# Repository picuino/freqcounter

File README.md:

Frequency counter
=================
This is a cheap and simple but powerful frequency counter capable 
of measurements of frequency with 8 digits of resolution every second
(9 digits of resolution in 10 second averages).

This frequency counter is based on a little **PIC 16F18446** a 
16x2 LCD display (optional) and USB-Serial interface with PC.

All the programs and hardware designs are free, open source and
open hardware.

The frequency counter have a Command Line Interface via serial 
communications for manage multiple internal options. 
You can read more in [Command Line Interface help](docs/commands.md)

You can mount the frequency counter over a breadboard with this simple 
[schematic](breadboard/kicad/freqcounter_16F18446.pdf)
with a cost of few dollars.
The LDC display is optional. All the info is sended via serial.

Specifications
--------------
* Input frequency range: 0.01 Hz to 15MHz
* Resolution: 8 digits per second (10ns of resolution) at all frequencies.
* Precision: 0.1PPM with simple crystal and calibration.
* Number of inputs: 2 TTL inputs + 1 Zero Cross Detection input
* Output: Frequency or Period, time and pulses counted.
* Phase delay: between 2 inputs with 10ns of resolution.
* Gate times: 1 second and 0.1 seconds.
* Output: via LCD (optional) and serial UART.
* Autocalibration: with 1PPS signal or with 10MHz signal.
* Reciprocal counting: allow calculate lower frequencies with decimals.
* Continuous timestamp: allow frequency averages without error.
* Frequency autorange from Mega Hertz to milli Hertz.
* Adaptable system frequency without reprogramming (8MHz internal or 5MHz external)
* Command Line Interface: via USB-serial communications for configuring options.
* Input levels: between 0.8v (LOW) and 3.1V (HIGH).
* Power Supply: 5 volts.
* DIY: you can mount it with a breadboard and one crystal oscillator.

Images
------
Example of frequency meter conected to an Arduino.
Arduino gives power and serial communications with PC.

Orange cables are the 2 TTL inputs.

[Full image](images/IMG_20200427_143115.jpg)

Licenses
--------

* Creative Commons Atribution-ShareAlike version 4, for hardware designs,
  texts, photograps, layouts, schematics, and similar.

* GNU General Public License version 3, for microcontroller 
  and computer programs.

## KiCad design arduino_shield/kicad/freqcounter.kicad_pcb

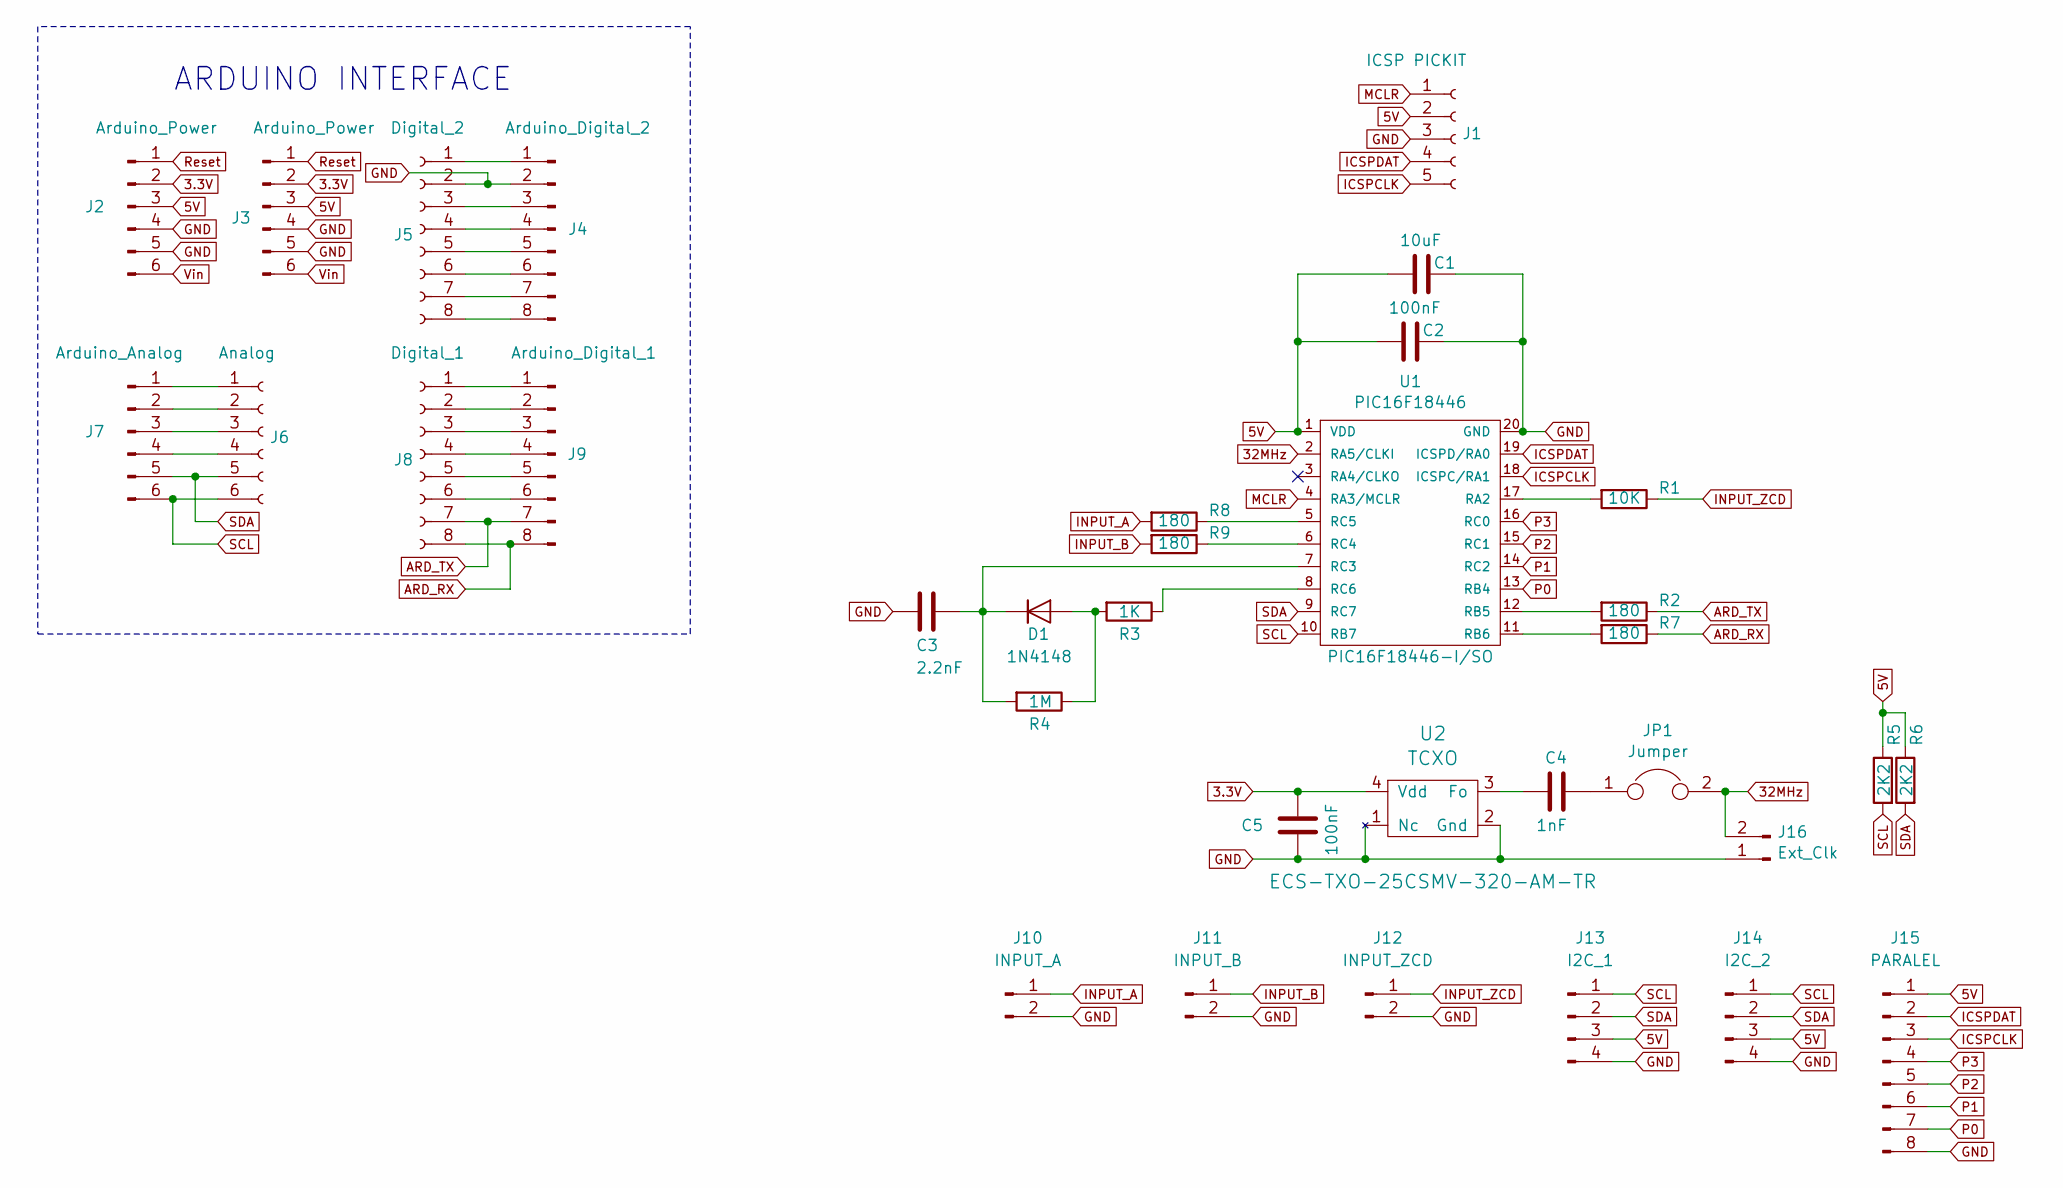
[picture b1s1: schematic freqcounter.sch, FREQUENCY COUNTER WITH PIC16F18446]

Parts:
C1: 10uF; C_0805_2012Metric_Pad1.15x1.40mm_HandSolder
C2, C5: 100nF; C_0805_2012Metric_Pad1.15x1.40mm_HandSolder
C3: 2.2nF; C_0805_2012Metric_Pad1.15x1.40mm_HandSolder
C4: 1nF; C_0805_2012Metric_Pad1.15x1.40mm_HandSolder
D1: 1N4148; SOD-80_HandSolder
J1: ICSP PICKIT; PinHeader_1x05_P2.54mm_Vertical
J2, J3: Arduino_Power; Connector_1x06
J4: Arduino_Digital_2; Connector_1x08
J5: Digital_2; Connector_1x08
J6: Analog; Connector_1x06
J7: Arduino_Analog; Connector_1x06
J8: Digital_1; Connector_1x08
J9: Arduino_Digital_1; Connector_1x08
J10: INPUT_A; PinHeader_1x02_P2.54mm_Vertical
J11: INPUT_B; PinHeader_1x02_P2.54mm_Vertical
J12: INPUT_ZCD; PinHeader_1x02_P2.54mm_Vertical
J13: I2C_1; PinHeader_1x04_P2.54mm_Vertical
J14: I2C_2; PinHeader_1x04_P2.54mm_Vertical
J15: PARALEL; Connector_1x08
J16: Ext_Clk; PinHeader_1x02
JP1: Jumper; PinHeader_1x02
R1: 10K; R_0805_2012Metric_Pad1.15x1.40mm_HandSolder
R2, R7, R8, R9: 180; R_0805_2012Metric_Pad1.15x1.40mm_HandSolder
R3: 1K; R_0805_2012Metric_Pad1.15x1.40mm_HandSolder
R4: 1M; R_0805_2012Metric_Pad1.15x1.40mm_HandSolder
R5, R6: 2K2; R_0805_2012Metric_Pad1.15x1.40mm_HandSolder
U1: PIC16F18446; SOIC-20W_7.5x12.8mm_P1.27mm
U2: TCXO; TCXO-5032

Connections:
3.3V: C5.2, J2.2, J3.2, U2.4 (Vdd)
5V: C1.2, C2.2, J1.2, J2.3, J3.3, J13.3, J14.3, J15.1, R5.1, R6.1, U1.1 (VDD)
32MHz: J16.2, JP1.2, U1.2 (RA5/CLKI)
ARD_RX: J8.8, J9.8, R7.1
ARD_TX: J8.7, J9.7, R2.1
GND: C1.1, C2.1, C3.2, C5.1, J1.3, J2.4, J2.5, J3.4, J3.5, J4.2, J5.2, J10.2, J11.2, J12.2, J13.4, J14.4, J15.8, J16.1, U1.20 (GND), U2.1 (Nc), U2.2 (Gnd)
ICSPCLK: J1.5, J15.3, U1.18 (ICSPC/RA1)
ICSPDAT: J1.4, J15.2, U1.19 (ICSPD/RA0)
INPUT_A: J10.1, R8.2
INPUT_B: J11.1, R9.2
INPUT_ZCD: J12.1, R1.1
MCLR: J1.1, U1.4 (RA3/MCLR)
unnamed: C3.1, D1.1 (K), R4.2, U1.7 (RC3)
unnamed: C4.1, U2.3 (Fo)
unnamed: C4.2, JP1.1
unnamed: D1.2 (A), R3.2, R4.1
unnamed: J4.1, J5.1
unnamed: J4.3, J5.3
unnamed: J4.4, J5.4
unnamed: J4.5, J5.5
unnamed: J4.6, J5.6
unnamed: J4.7, J5.7
unnamed: J4.8, J5.8
unnamed: J6.1, J7.1
unnamed: J6.2, J7.2
unnamed: J6.3, J7.3
unnamed: J6.4, J7.4
unnamed: J8.1, J9.1
unnamed: J8.2, J9.2
unnamed: J8.3, J9.3
unnamed: J8.4, J9.4
unnamed: J8.5, J9.5
unnamed: J8.6, J9.6
unnamed: R1.2, U1.17 (RA2)
unnamed: R2.2, U1.12 (RB5)
unnamed: R3.1, U1.8 (RC6)
unnamed: R7.2, U1.11 (RB6)
unnamed: R8.1, U1.5 (RC5)
unnamed: R9.1, U1.6 (RC4)
P0: J15.7, U1.13 (RB4)
P1: J15.6, U1.14 (RC2)
P2: J15.5, U1.15 (RC1)
P3: J15.4, U1.16 (RC0)
Reset: J2.1, J3.1
SCL: J6.6, J7.6, J13.1, J14.1, R5.2, U1.10 (RB7)
SDA: J6.5, J7.5, J13.2, J14.2, R6.2, U1.9 (RC7)
Vin: J2.6, J3.6

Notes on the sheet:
ARDUINO INTERFACE

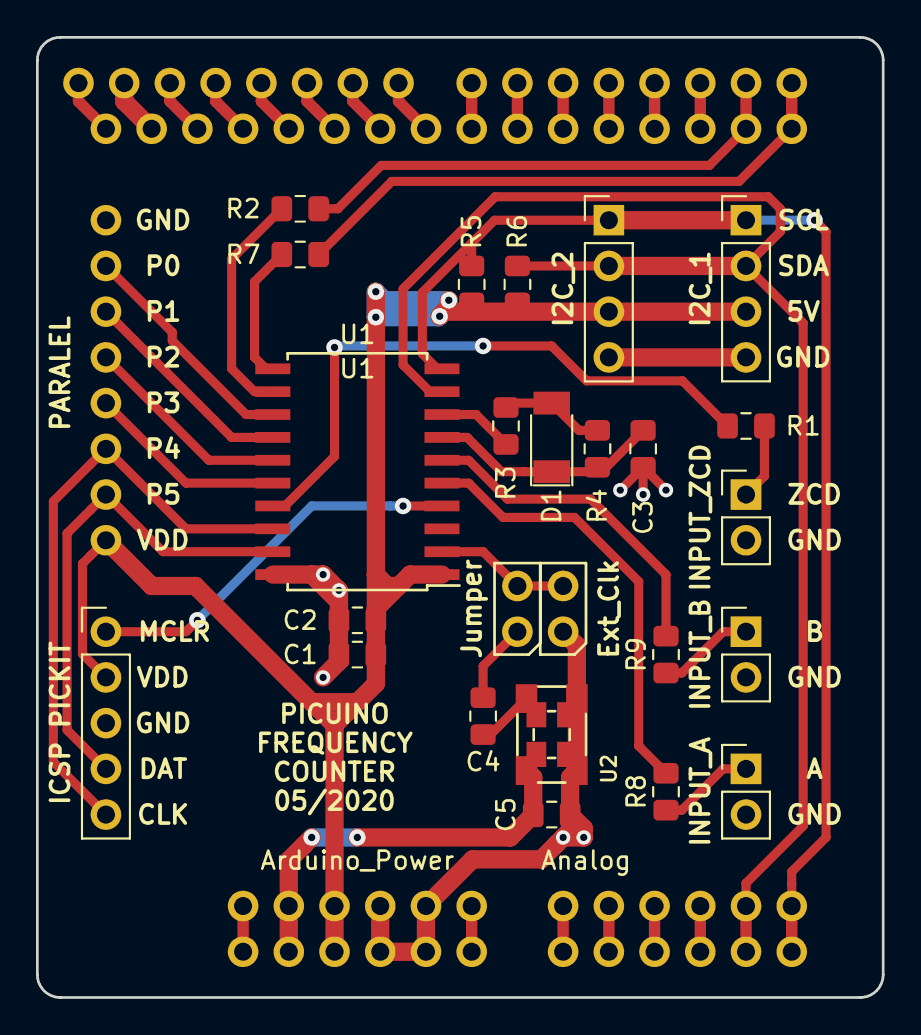
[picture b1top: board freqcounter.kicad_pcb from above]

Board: 2 copper layers, 47.0 x 53.3 mm, 34 parts (0 on the bottom side), 47 nets.

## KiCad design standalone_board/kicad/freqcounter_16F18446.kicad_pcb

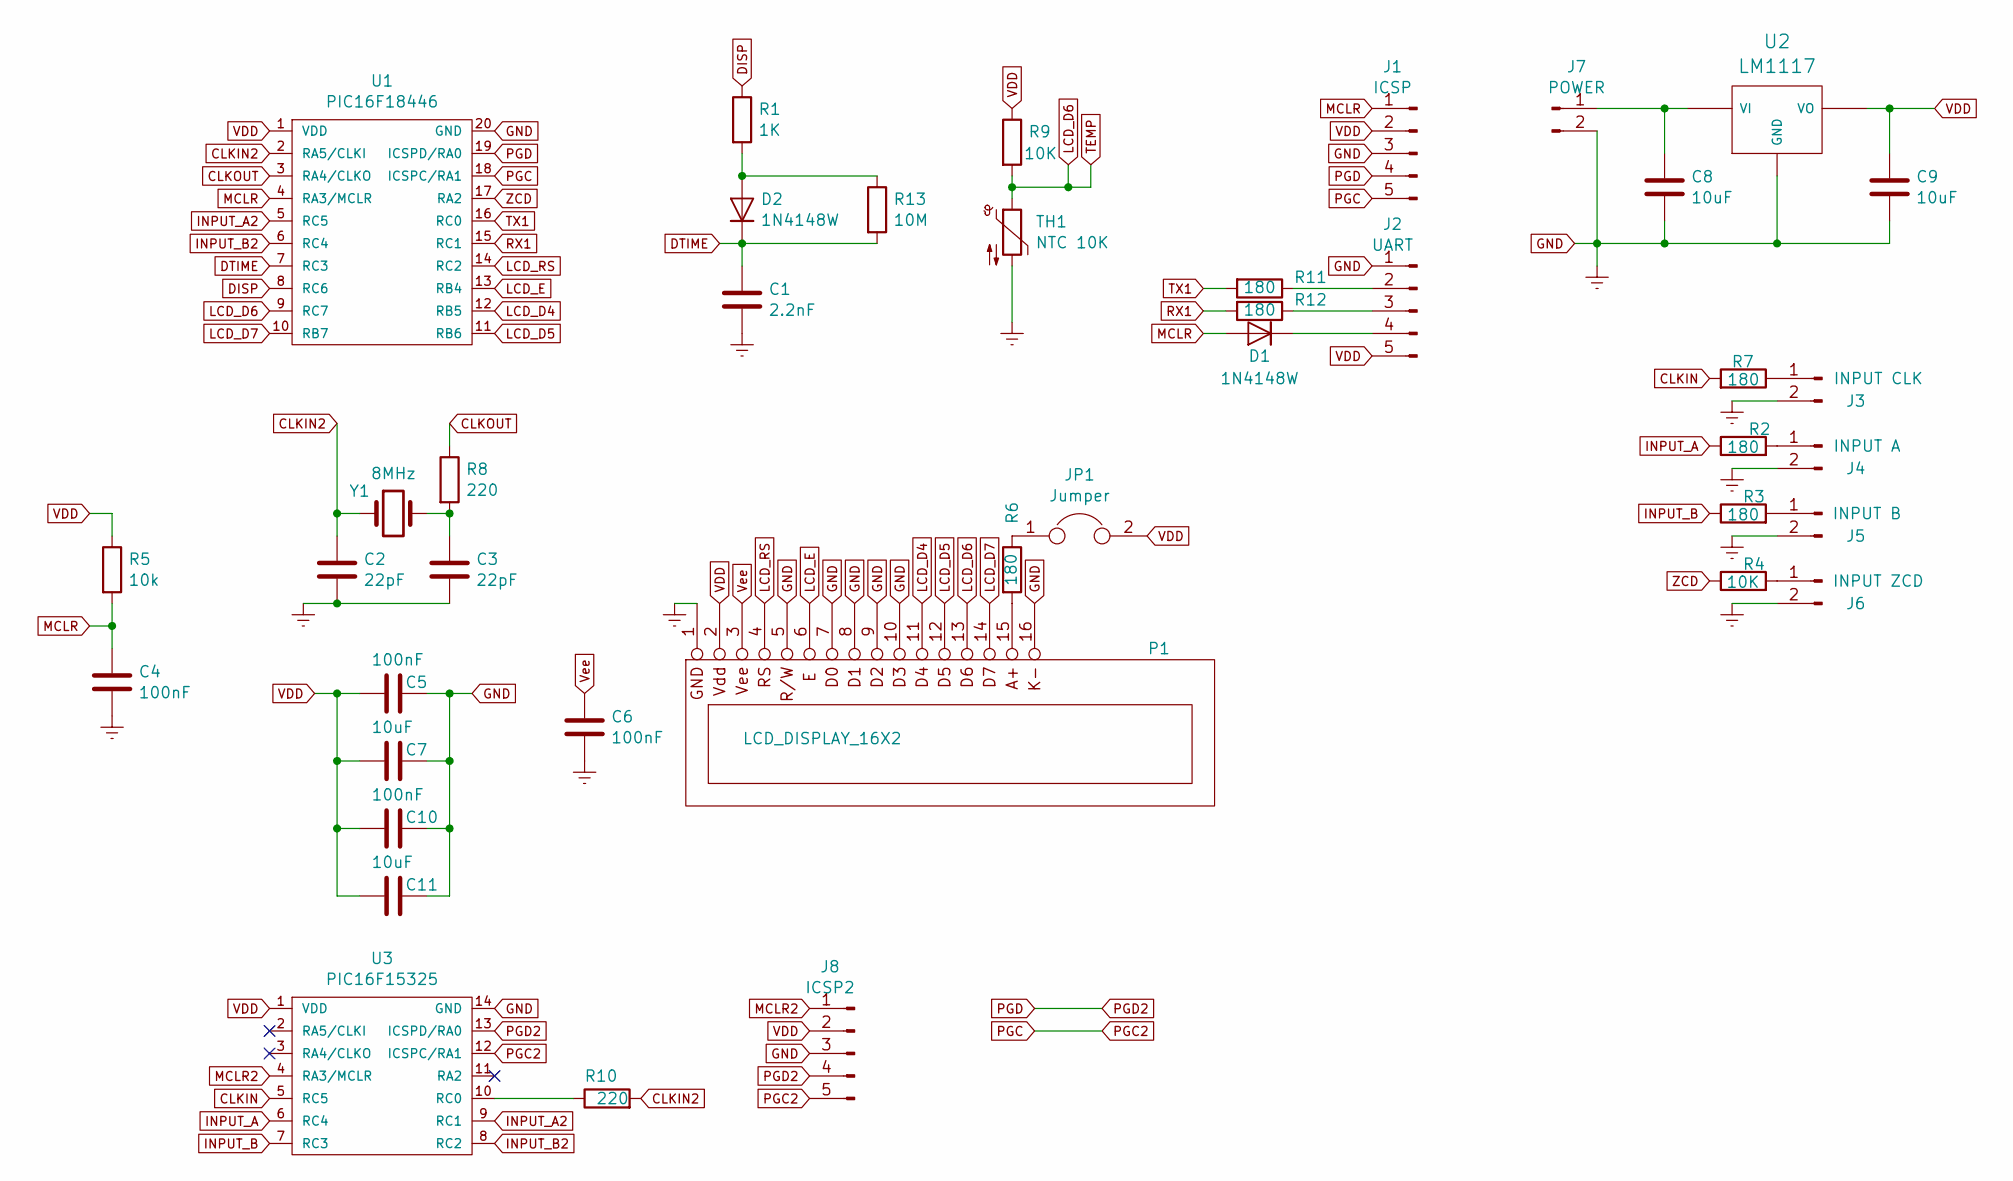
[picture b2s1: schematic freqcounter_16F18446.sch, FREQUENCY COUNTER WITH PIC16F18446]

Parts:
C1: 2.2nF; C_0805_2012Metric_Pad1.15x1.40mm_HandSolder
C2, C3: 22pF; C_0805_2012Metric_Pad1.15x1.40mm_HandSolder
C4, C5, C6, C10: 100nF; C_0805_2012Metric_Pad1.15x1.40mm_HandSolder
C7, C11: 10uF; C_0805_2012Metric_Pad1.15x1.40mm_HandSolder
C8, C9: 10uF; C_Rect_L4.6mm_W5.5mm_P2.50mm_MKS02_FKP02
D1, D2: 1N4148W; D_SOD-123
J1: ICSP; PinHeader_1x05_P2.54mm_Vertical
J2: UART; PinHeader_1x05_P2.54mm_Vertical
J3: INPUT CLK; PinHeader_1x02_P2.54mm_Vertical
J4: INPUT A; PinHeader_1x02_P2.54mm_Vertical
J5: INPUT B; PinHeader_1x02_P2.54mm_Vertical
J6: INPUT ZCD; PinHeader_1x02_P2.54mm_Vertical
J7: POWER; PinHeader_1x02_P2.54mm_Vertical
J8: ICSP2; PinHeader_1x05_P2.54mm_Vertical
JP1: Jumper; PinHeader_1x02_P2.54mm_Vertical
P1: LCD_DISPLAY_16X2; PinHeader_1x16_P2.54mm_Vertical
R1: 1K; R_0805_2012Metric_Pad1.15x1.40mm_HandSolder
R2, R3, R6, R7, R11, R12: 180; R_0805_2012Metric_Pad1.15x1.40mm_HandSolder
R4, R9: 10K; R_0805_2012Metric_Pad1.15x1.40mm_HandSolder
R5: 10k; R_0805_2012Metric_Pad1.15x1.40mm_HandSolder
R8, R10: 220; R_0805_2012Metric_Pad1.15x1.40mm_HandSolder
R13: 10M; R_0805_2012Metric_Pad1.15x1.40mm_HandSolder
TH1: NTC 10K; R_0805_2012Metric_Pad1.15x1.40mm_HandSolder
U1: PIC16F18446; SOIC-20W_7.5x12.8mm_P1.27mm
U2: LM1117; SOT223_LM1117
U3: PIC16F15325
Y1: 8MHz; Crystal_HC18-U_Vertical

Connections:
CLKIN: R7.2, U3.5 (RC5)
CLKIN2: C2.1, R10.2, U1.2 (RA5/CLKI), Y1.1
CLKOUT: R8.1, U1.3 (RA4/CLKO)
DISP: R1.1, U1.8 (RC6)
DTIME: C1.1, D2.1 (K), R13.2, U1.7 (RC3)
GND: C1.2, C2.2, C3.2, C4.2, C5.1, C6.2, C7.1, C8.2, C9.2, C10.1, C11.1, J1.3, J2.1, J3.2, J4.2, J5.2, J6.2, J7.2, J8.3, P1.1, P1.5, P1.7, P1.8, P1.9, P1.10, P1.16, TH1.2, U1.20 (GND), U2.GND, U3.14 (GND)
INPUT_A: R2.1, U3.6 (RC4)
INPUT_A2: U1.5 (RC5), U3.9 (RC1)
INPUT_B: R3.1, U3.7 (RC3)
INPUT_B2: U1.6 (RC4), U3.8 (RC2)
LCD_D4: P1.11, U1.12 (RB5)
LCD_D5: P1.12, U1.11 (RB6)
LCD_D6: P1.13, R9.2, TH1.1, U1.9 (RC7)
LCD_D7: P1.14, U1.10 (RB7)
LCD_E: P1.6, U1.13 (RB4)
LCD_RS: P1.4, U1.14 (RC2)
MCLR: C4.1, D1.2 (A), J1.1, R5.2, U1.4 (RA3/MCLR)
MCLR2: J8.1, U3.4 (RA3/MCLR)
unnamed: C3.1, R8.2, Y1.2
unnamed: C8.1, J7.1, U2.VI
unnamed: D1.1 (K), J2.4
unnamed: D2.2 (A), R1.2, R13.1
unnamed: J2.2, R11.1
unnamed: J2.3, R12.1
unnamed: J3.1, R7.1
unnamed: J4.1, R2.2
unnamed: J5.1, R3.2
unnamed: J6.1, R4.2
unnamed: JP1.1, R6.1
unnamed: P1.15, R6.2
unnamed: R10.1, U3.10 (RC0)
PGC: J1.5, J8.5, U1.18 (ICSPC/RA1), U3.12 (ICSPC/RA1)
PGD: J1.4, J8.4, U1.19 (ICSPD/RA0), U3.13 (ICSPD/RA0)
RX1: R12.2, U1.15 (RC1)
TX1: R11.2, U1.16 (RC0)
VDD: C5.2, C7.2, C9.1, C10.2, C11.2, J1.2, J2.5, J8.2, JP1.2, P1.2, R5.1, R9.1, U1.1 (VDD), U2.VO, U3.1 (VDD)
Vee: C6.1, P1.3
ZCD: R4.1, U1.17 (RA2)

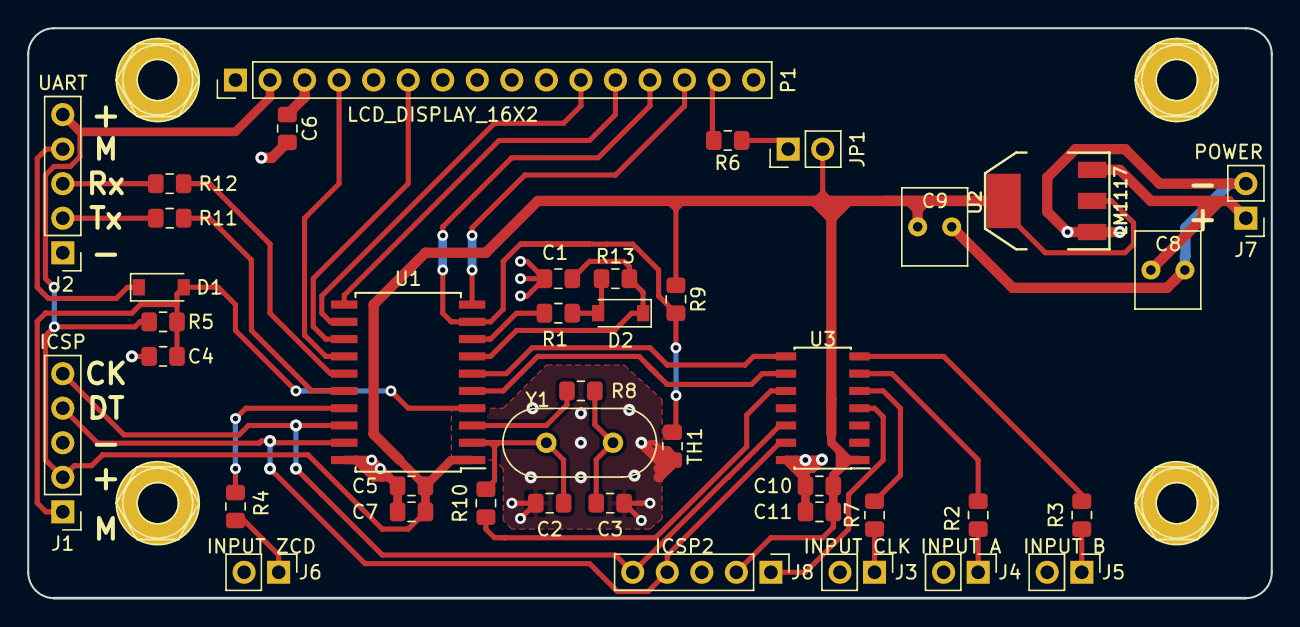
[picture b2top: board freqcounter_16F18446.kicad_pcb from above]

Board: 2 copper layers, 91.4 x 41.9 mm, 45 parts (0 on the bottom side), 38 nets.

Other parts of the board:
M3, M3#2, M3#3, M3#4: SCREW_M3

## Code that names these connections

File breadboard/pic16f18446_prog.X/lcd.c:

/*
 * LCD 16x2 manage routines
 *
 * Author: Carlos Pardo
 *
 * This file is subject to the terms and conditions of the GNU General
 * Public License Version 3. See the file "COPYING" in the main directory
 * of this archive for more details.
 *
 */

#include <xc.h>
#include "config.h"
#include "lcd.h"


/****************************************************************************
      DEFINITIONS
 ****************************************************************************/

#define LCD_RS     LATBbits.LATB4         // LCD CONTROL BIT. Control/data mode
#define LCD_E      LATCbits.LATC2         // LCD CONTROL BIT. Enable
#define LCD_D4     LATCbits.LATC1         // LCD DATA BIT
#define LCD_D5     LATCbits.LATC0         // LCD DATA BIT
#define LCD_D6     LATAbits.LATA1         // LCD DATA BIT
#define LCD_D7     LATAbits.LATA0         // LCD DATA BIT

#define LCD_TRIS_OUT()   TRISC &= ~((1<<0)+(1<<1)+(1<<2)); TRISB &= ~((1<<4)); TRISA &= ~((1<<0)+(1<<1))
#define LCD_TRIS_IN()    TRISC |= ((1<<0)+(1<<1)+(1<<2)); TRISB |= ((1<<4)); TRISA |= ((1<<0)+(1<<1))


/****************************************************************************
      LCD ROUTINES
 ****************************************************************************/


/*
 *  INITIALIZE LCD IN 4-BIT MODE AND SET PREFERENCES
 */
void lcd_init(void) {

   // Init control pins
   LCD_RS = 0; // LCD IN CONTROL MODE
   LCD_E = 0;

   // Init data pins
   LCD_D4 = 0;
   LCD_D5 = 0;
   LCD_D6 = 0;
   LCD_D7 = 0;

   // Init control and data pins
   LCD_TRIS_OUT();

   // Wait at least 20 ms after Vdd rises to 4.5 V
   __delay_ms(50);

   // Reset procedure through software
   lcd_putnibble(0x30); // 8 bits mode
   __delay_us(4500);
   lcd_putnibble(0x30); // 8 bits mode
   __delay_us(4500);
   lcd_putnibble(0x30); // 8 bits mode
   __delay_us(150);
   lcd_putnibble(0x20); // 4 bits mode

   // CONFIGURE LCD
   lcd_putctrl(LCD_FUNCTION_SET + LCD_4_BIT_INTERFACE
           + LCD_2_LINES + LCD_5X8_DOTS);
   lcd_putctrl(LCD_DISPLAY_CONTROL + LCD_DISPLAY_ON
           + LCD_CURSOR_OFF + LCD_CURSOR_BLINK_OFF);
   lcd_clear();
   lcd_putctrl(LCD_ENTRY_MODE + LCD_ENTRY_LEFT + LCD_ENTRY_SHIFT_OFF);
}


/*
 * Clears entire display and sets DDRAM address 0 in address
 * counter
 */
void lcd_clear(void) {
   lcd_putctrl(0b00000001); // CLEAR DISPLAY.
   __delay_us(2000); // Execution time > 1.6 ms
}


/*
 * Sets DDRAM address 0 in address counter. Also returns
 * display from being shifted to original position. DDRAM
 * contents remain unchanged
 */
void lcd_home(void) {
   lcd_putctrl(0b00000010); // CURSOR TO POSITION 0
   __delay_us(2000); // Execution time > 1.6 ms
}


/*
 * Set address of cursor in LCD
 * Send addr to DDRAM address register
 * First line inits at address 0
 * Second line inits at address 40
 */
void lcd_goto(unsigned char x) {
   lcd_putctrl(0b10000000 + x); // CURSOR TO POSITION x
}


/*
 * Send control code to LCD
 */
void lcd_putctrl(unsigned char c) {
   LCD_RS = 0; // LCD IN CONTROL MODE
   lcd_putbyte(c);
}


/*
 * Send character to LCD
 */
void lcd_putc(unsigned char c) {
   LCD_RS = 1; // LCD IN DATA MODE
   lcd_putbyte(c);
}


/*
 * Send string in ram to LCD
 */
void lcd_puts_ram(char *str) {
   while (*str) {
      lcd_putc(*str++);
   }
}


/*
 * Send constant string to LCD
 */
void lcd_puts(const char *str) {
   while (*str) {
      lcd_putc(*str++);
   }
}


/*
 * Send byte to LCD
 */
void lcd_putbyte(unsigned char c) {
   LCD_TRIS_OUT();
   lcd_putnibble(c);
   lcd_putnibble(c << 4);
   LCD_D4 = 0;
   LCD_D5 = 0;
   LCD_D6 = 0;
   LCD_D7 = 0;
}


/*
 * Send high nibble of character 'c' to LCD
 */
void lcd_putnibble(unsigned char c) {
   if (c & 0x10) LCD_D4 = 1;
   else LCD_D4 = 0;
   if (c & 0x20) LCD_D5 = 1;
   else LCD_D5 = 0;
   if (c & 0x40) LCD_D6 = 1;
   else LCD_D6 = 0;
   if (c & 0x80) LCD_D7 = 1;
   else LCD_D7 = 0;
   lcd_enable();
}


/*
 * ENABLE LCD
 * Send enable signal to LCD
 */
void lcd_enable(void) {
   LCD_E = 0;
   __delay_us(1); // Enable signal must be set 1us min
   LCD_E = 1;
   __delay_us(1); // Enable signal must be set 1us min
   LCD_E = 0;
   __delay_us(140); // Command need > 37us to settle
}

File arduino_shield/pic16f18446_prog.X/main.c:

/*
 * Frequency counter with PIC16F18446
 *
 * Author: Carlos Pardo
 *
 * Inputs:
 *    RC5 (Pin_5) Input A
 *    RC4 (Pin_6) Input B
 *
 * UART:
 *   TX on RA2 (Pin_17)
 *   RX on RC0 (Pin_16)
 *
 *
 * TO-DO:
 *  - Refactor and clean code
 *
 * License:
 *
 * This file is subject to the terms and conditions of the GNU General
 * Public License Version 3. See the file "COPYING" in the main directory
 * of this archive for more details.
 *
 */

#include <xc.h>
#include "config.h"
#include "peripheral.h"
#include "timers.h"
#include "math48.h"
#include "uart.h"
#include "counter.h"
#include "lcd.h"
#include "eprom.h"
#include "command.h"
#include "calibration.h"

extern options_t options;


/*
 *  INTERRUPT SERVICE ROUTINE
 */
void __interrupt() isr(void) {

   // Interrupt service routine of timers
   timers_isr();

   // Interrupt service routine of UART
   uart_isr();
}


/*
 *  Inits CPU
 */
void cpu_init(void) {
   // Disable interrupts
   INTCON = 0;

   // Oscillator
   WDTCON0bits.SWDTEN = 0; // Watchdog disabled

   // Init ports
   ANSELA = 0;
   ANSELB = 0;
   ANSELC = 0;
   LATA = 0x00;
   LATB = 0x00;
   LATC = 0x00;
   TRISA = 0xFF;
   TRISB = 0xFF;
   TRISC = 0xFF;

   // Weak pull up resistors
   WPUA = 0;
   WPUB = 0;
   WPUC = 0;
   WPUAbits.WPUA3 = 1; // MCLR wpu

   // Enable interrupts
   INTCONbits.PEIE = 1;
   INTCONbits.GIE = 0;
}

/*
 *  MAIN FUNCTION
 */
void main(void) {
   extern char counter_reset_inputs;

   // Configure System clock frequency
   options.system_clk_mhz = 8;

   // Init CPU and peripherals
   cpu_init();
   pps_init();
   uart_init();
   timer0_init();
   lcd_init();
   adc_init();
   clc_init();
   zcd_init();

   // Enable interrupts and send wellcome message
   INTCONbits.GIE = 1;
   counter_wait_period();
   cmd_version();
   lcd_puts("System OK");


   // Init modules
   cmd_init();
   calibrate_init();
   counter_init();

   // Frequency counter main loop
   while (1) {
      counter_prescaler_channel_a();
      counter_prescaler_channel_b();

      counter_wait_period();
      system_speed();

      if (counter_reset_inputs == 1) {
         counter_reset_inputs = 0;
         uart_fputs("# Reset counters\n");
         counter_reset();
         continue;
      }

      counter_save_old_values();
      ctmu_calibrate();
      counter_capture_channels();

      counter_print_channel_a();
      counter_print_channel_b();
      counter_print_end();

      // Autocalibrate with the last signal measured
      counter_1pps_autocalibrate();
      counter_10mhz_autocalibrate();
   }
}

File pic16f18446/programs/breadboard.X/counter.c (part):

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void counter_options_init(void) {
   options.autocalibrate = 0;
   options.ctmu_enable = 1;
   options.input_a = 1;
   options.input_b = 0;
   options.input_zcd = 0;
   options.fast_measure = 0;

   options.print_pulses = 0;
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
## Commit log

2020-04-24 Added gitignore
2020-04-24 Edited README.md
2020-04-24 Refactor code.
2020-04-24 README.md edited
2020-04-24 Edited info
2020-04-24 Added Tera prefix
2020-04-24 Added hex file for direct programming pic microcontroller.
2020-04-24 Comment program
2020-04-24 Change initial character in comments "#". Added message with github address and contact info.
2020-04-24 Updated firmware
2020-04-25 Move files and directories
2020-04-25 Move files and bugfix program project.
2020-04-25 Updated kicad schematic
2020-04-27 Bugfix makefile for make thumbnails
2020-04-27 Images of frequency counter on a breadboard with Arduino.
2020-04-27 Reduced delay time between channel captures.
2020-04-28 Updated Arduino shield schematic and PCB
2020-04-28 Updated Schematic and PCB
2020-04-28 Bugfix schematic and PCB
2020-04-30 Arduino Shield PCB designed
2020-04-30 Bugfix Arduino-Shield PCB
2020-04-30 Bugfix Arduino-Shield Schematic and PCB
2020-05-01 Updated Arduino-Shield Schematic and PCB
2020-05-01 Update Hex file
2020-05-02 Updated schematic
2020-05-02 Added program to Arduino-shield
2020-05-02 Added program for disconecting TX pin and use Arduino as USB-Serial interface
2020-05-02 Updated project. Changed UART and LCD pins
2020-05-04 Updated schematic and PCB with LCD connector
2020-05-04 Bugfix schematic and PCB with LCD connector

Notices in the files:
arduino_shield/kicad/freqcounter.sch:
License CC BY-SA 4.0
